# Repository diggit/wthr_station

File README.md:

#Weather station#
============

Final project on secondary school, meteorological/weather station with web access.

## Divided into two main parts:
* Sensors with MCU outside, collecting various values. Newly extended by temperature sensor board (3 ICs). 
* Software running on RaspberryPi, grabs values from sensor "module",
    stores them in mysql database and publishes them on web.

## Material here :

* In **multi_sens** directory are complete sources for sensor module with libraries
  can be build with avr-gcc (tested on (arch)linux with 4.8.0).

* In **root** is python script. Periodicaly executed by cron (every 1O mins and 1min). After execution sends request to sensor
  module (serial communication). Returned structured string is decoded into mesured values. Then script stores values
  into mysql database for further usage and requests some last values. From returned values is generated javascript file
  containing array fileled with values. (used by web page)
  Data from minute updates are used for webpage header only. The are not stored for further usage.

* In **web_app** is web application's root, so index.html and value file(s) generated by script described above are here.
  Design itself is not cool or awesome but works as it should.

* In **electonics** are schematics, PSB designs, their exports for printing, etc.

* In **designs** are models of housing for sensor module now, openscad source and stls of individual parts.
  STLs may be out of date. Use openscad to get up to date design of housing.

* In **photo** are photos of station and it's parts. It really exists!

## STATUS
* working, needs webpage design improvement
* look at: http://m72.dkm.cz or http://meteo-chodov.tk
* ~~Temperature measurements from BMP085 are quite accurate.~~ Sometimes happen, that sensor returs 0°C instead of real value. I was unable to fix it up.
* Extension board with 3 temperature sensors ADT7410 16bit i2c ICs is working. BMP085 reports higher temperature, 1.5°C (approx) above new sensor's value. 
* my 3D printer is not functional now, but I prepared top housing part for new light sensor. This sensor is in queue.

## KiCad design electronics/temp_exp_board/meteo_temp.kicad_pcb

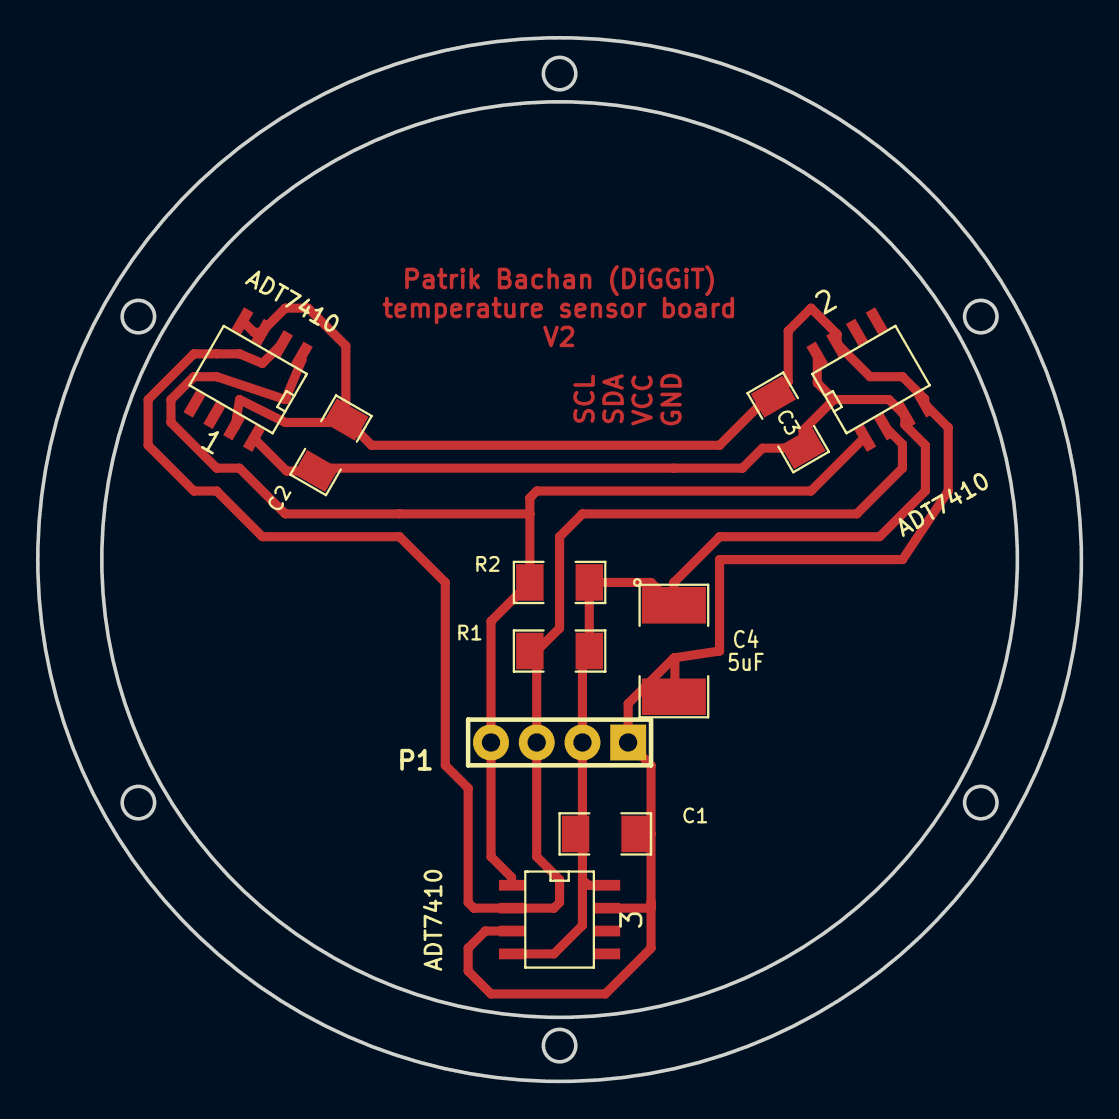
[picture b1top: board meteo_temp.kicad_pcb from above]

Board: 2 copper layers, 58.0 x 58.0 mm, 10 parts (0 on the bottom side), 4 nets.

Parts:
1, 2, 3: ADT7410; SO8E
C1, C2, C3: 100n; SM1206
C4: 5uF; SM1812L
P1: MAIN; PIN_ARRAY_4x1
R1, R2: 5k; SM1206

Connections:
unnamed: 1.1, 2.1, 3.1, P1.4, R2.2
unnamed: 1.2, 2.2, 3.2, P1.3, R1.2
unnamed: 1.8, 2.3, 2.8, 3.4, 3.8, C1.1, C2.1, C3.1, C4.1, P1.2, R1.1, R2.1
unnamed: 1.3, 1.4, 1.7, 2.4, 2.7, 3.3, 3.7, C1.2, C2.2, C3.2, C4.2, P1.1

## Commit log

2012-12-05 temp. reading successful
2012-12-05 sign overflow fix, extended display functions
2012-12-06 code cleanup
2012-12-06 pressure read appended, val. differs from real, need fix
2012-12-06 untested example
2012-12-06 added magic offset, needs testing...
2012-12-06 data types rename
2012-12-07 code cleanup and division into libs
2012-12-08 code optimizations, desc. of functions
2012-12-08 UART output migration
2012-12-08 DHT11 support added, some code fixes
2012-12-08 repo cleanup
2012-12-08 uart functions moved away
2012-12-12 multiple DHTs, structured output, measure on request, IDLE in meantime
2012-12-25 minor changes
2012-12-25 note added
2013-01-05 software reset added
2013-01-05 PCB design, initial commit
2013-01-05 README update
2013-01-06 grabber script rewritten
2013-01-06 all 3 graphs now
2013-01-12 initial design push
2013-01-12 design export
2013-01-12 design output in stl
2013-01-19 design modifications
2013-01-27 rod mount finished
2013-01-27 minor fixes
2013-01-27 blocked multiple query, alpha release
2013-01-27 arduino BL, correct LED pin, shorter delay
2013-02-03 exporting into images now (with matplotlib)
2013-02-03 optional temp. and press. averaging
2013-02-03 design update
2013-02-03 garbage deleted
2013-02-18 export of last values
2013-02-18 error filter
2013-02-18 stores actual values and time
2013-02-18 design changes
2013-03-06 minute updates into js vars
2013-03-06 erro prevention delay
2013-03-06 complete model overview
2013-04-24 top part with window
2013-04-24 no changes
2013-04-24 getting prepared on temp. expansion board
2013-04-24 new expansion board for temp. sensors
2013-04-24 cleanup, removed no longer used libs
2013-04-24 commented #include of not xet finished expansion board lib
2013-04-25 better comented code, error handling improvement in progress
2013-04-25 updated description
2013-05-01 added support for extension temperature board
2013-05-01 initial commit of EXt temp.board library
2013-05-01 loop moved away from main.c
2013-05-01 just some testing
2013-05-01 part for mounting onto tube, rod,... (vertical)
2013-05-01 status update
2013-05-01 actual appearance
2013-05-01 new directory
2013-05-02 date and time of compilation reporting at boot
2013-05-02 bugfix, wrong bitewise shift operation (artefact)
2013-05-02 strip unused functions
2013-05-02 code cleanup and debug messages update
2013-05-02 comments revision and cleanup
2013-05-18 switched default rendering opt.
2013-05-18 response error detection and warning on webpage
2013-05-18 testing
2013-05-18 new stle
2013-06-18 cron needs full path
2013-06-18 high temperature overflow fix
2013-07-08 typo fixed
2013-07-08 refreshed model
2013-07-08 new about page
2013-07-08 new contact page
2013-07-08 design improvement
2013-07-08 new ajay updating of values
2013-07-08 new file for actual values, plain text
2013-07-08 ajax script for refreshing values without page reloading
2013-07-08 new youtput file format
2013-07-08 modified testing values
2013-07-08 script for google map
2013-07-08 images and thumbnails for 'about' page
2013-07-08 folder for charts
2013-07-08 improved end of content
2013-07-08 html fixed
2013-07-08 dynamic chyrt realoading
2013-07-08 added chart realoding script
2013-07-08 func rename
2013-07-08 some testing images
2013-07-08 function name corrected
2014-08-07 cleanup and renaming
2014-08-09 status parsing
2014-08-09 timeouted, checksum validation
2014-08-09 sensor checking and skipping
2014-08-09 interrupt enable fix, newline func, macro merged
2014-08-09 verbose macros for debug
2014-08-09 BMP085 func separated, improved
2014-08-09 overal station state infos
2014-08-09 checking function, RW parameter to start func, timeout func separation
2014-08-09 timeout func added, macro cleanup
2014-08-09 c99 now, send reset char (R) to station before programming
2014-08-09 more config moved here
2014-08-09 massive rewrite, cleanup, HW checking,...
2014-08-09 tested some new values
2014-08-10 status message handling, chart style modified
2014-08-10 use status LED
2014-08-10 show status messages
2014-08-10 handle toggling status messages visibility
2014-08-10 new dark style
2014-08-10 blink just border when reloaded header
2014-08-10 new file format testing
2014-08-10 updated .gitignore
2014-08-13 text coor fixed
2014-11-26 forgotten update
2014-11-26 sign hot fix
2014-11-26 sign position fix
2014-11-26 return type fixed
2014-12-31 line smoothing
2014-12-31 more compatible list copy method
2016-08-10 Improve grabber_daemon script - cleanup - less dependencies - ...?
2018-12-10 add light sensor
2018-12-10 fix problems with uart and parsing
2018-12-10 fix semilog plots
2018-12-10 fix styling of light value in header
2018-12-10 more web app fixes
2018-12-10 fix parsing of actual data file
2018-12-13 use symlog to reach to 0
2018-12-13 fix typo from copy paste
2018-12-16 make date and time horizontal in plots
2018-12-16 improve date formatting
2018-12-16 change vertical size of plots
2018-12-16 more tweaks to plot size
2018-12-16 more tweaks to plot size, add missing hr
2018-12-16 add minimal bottom space to chart
2018-12-16 add missing hr in index, use tight_layout for plots
2019-01-25 cleanup ADT data conversion
